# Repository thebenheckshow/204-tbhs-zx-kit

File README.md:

# 204-tbhs-zx-kit

Ben has modded many old computers into gaming portables and in this episode Ben returns to an old friend - the ZX Spectrum. He gets started by creating a schematic in eagle and designing a small PCB. Ben will conclude his journey in part 2.

Episode 204: Ben Heck's ZX Spectrum 2.0 Part 1 http://www.element14.com/community/docs/DOC-78511/l/episode-204-ben-hecks-zx-spectrum-20-part-1-episode

Episode 206: Ben Heck's ZX Spectrum 2.0 Part 2 http://www.element14.com/community/docs/DOC-78741/l/episode-206-ben-hecks-zx-spectrum-20-part-2-episode

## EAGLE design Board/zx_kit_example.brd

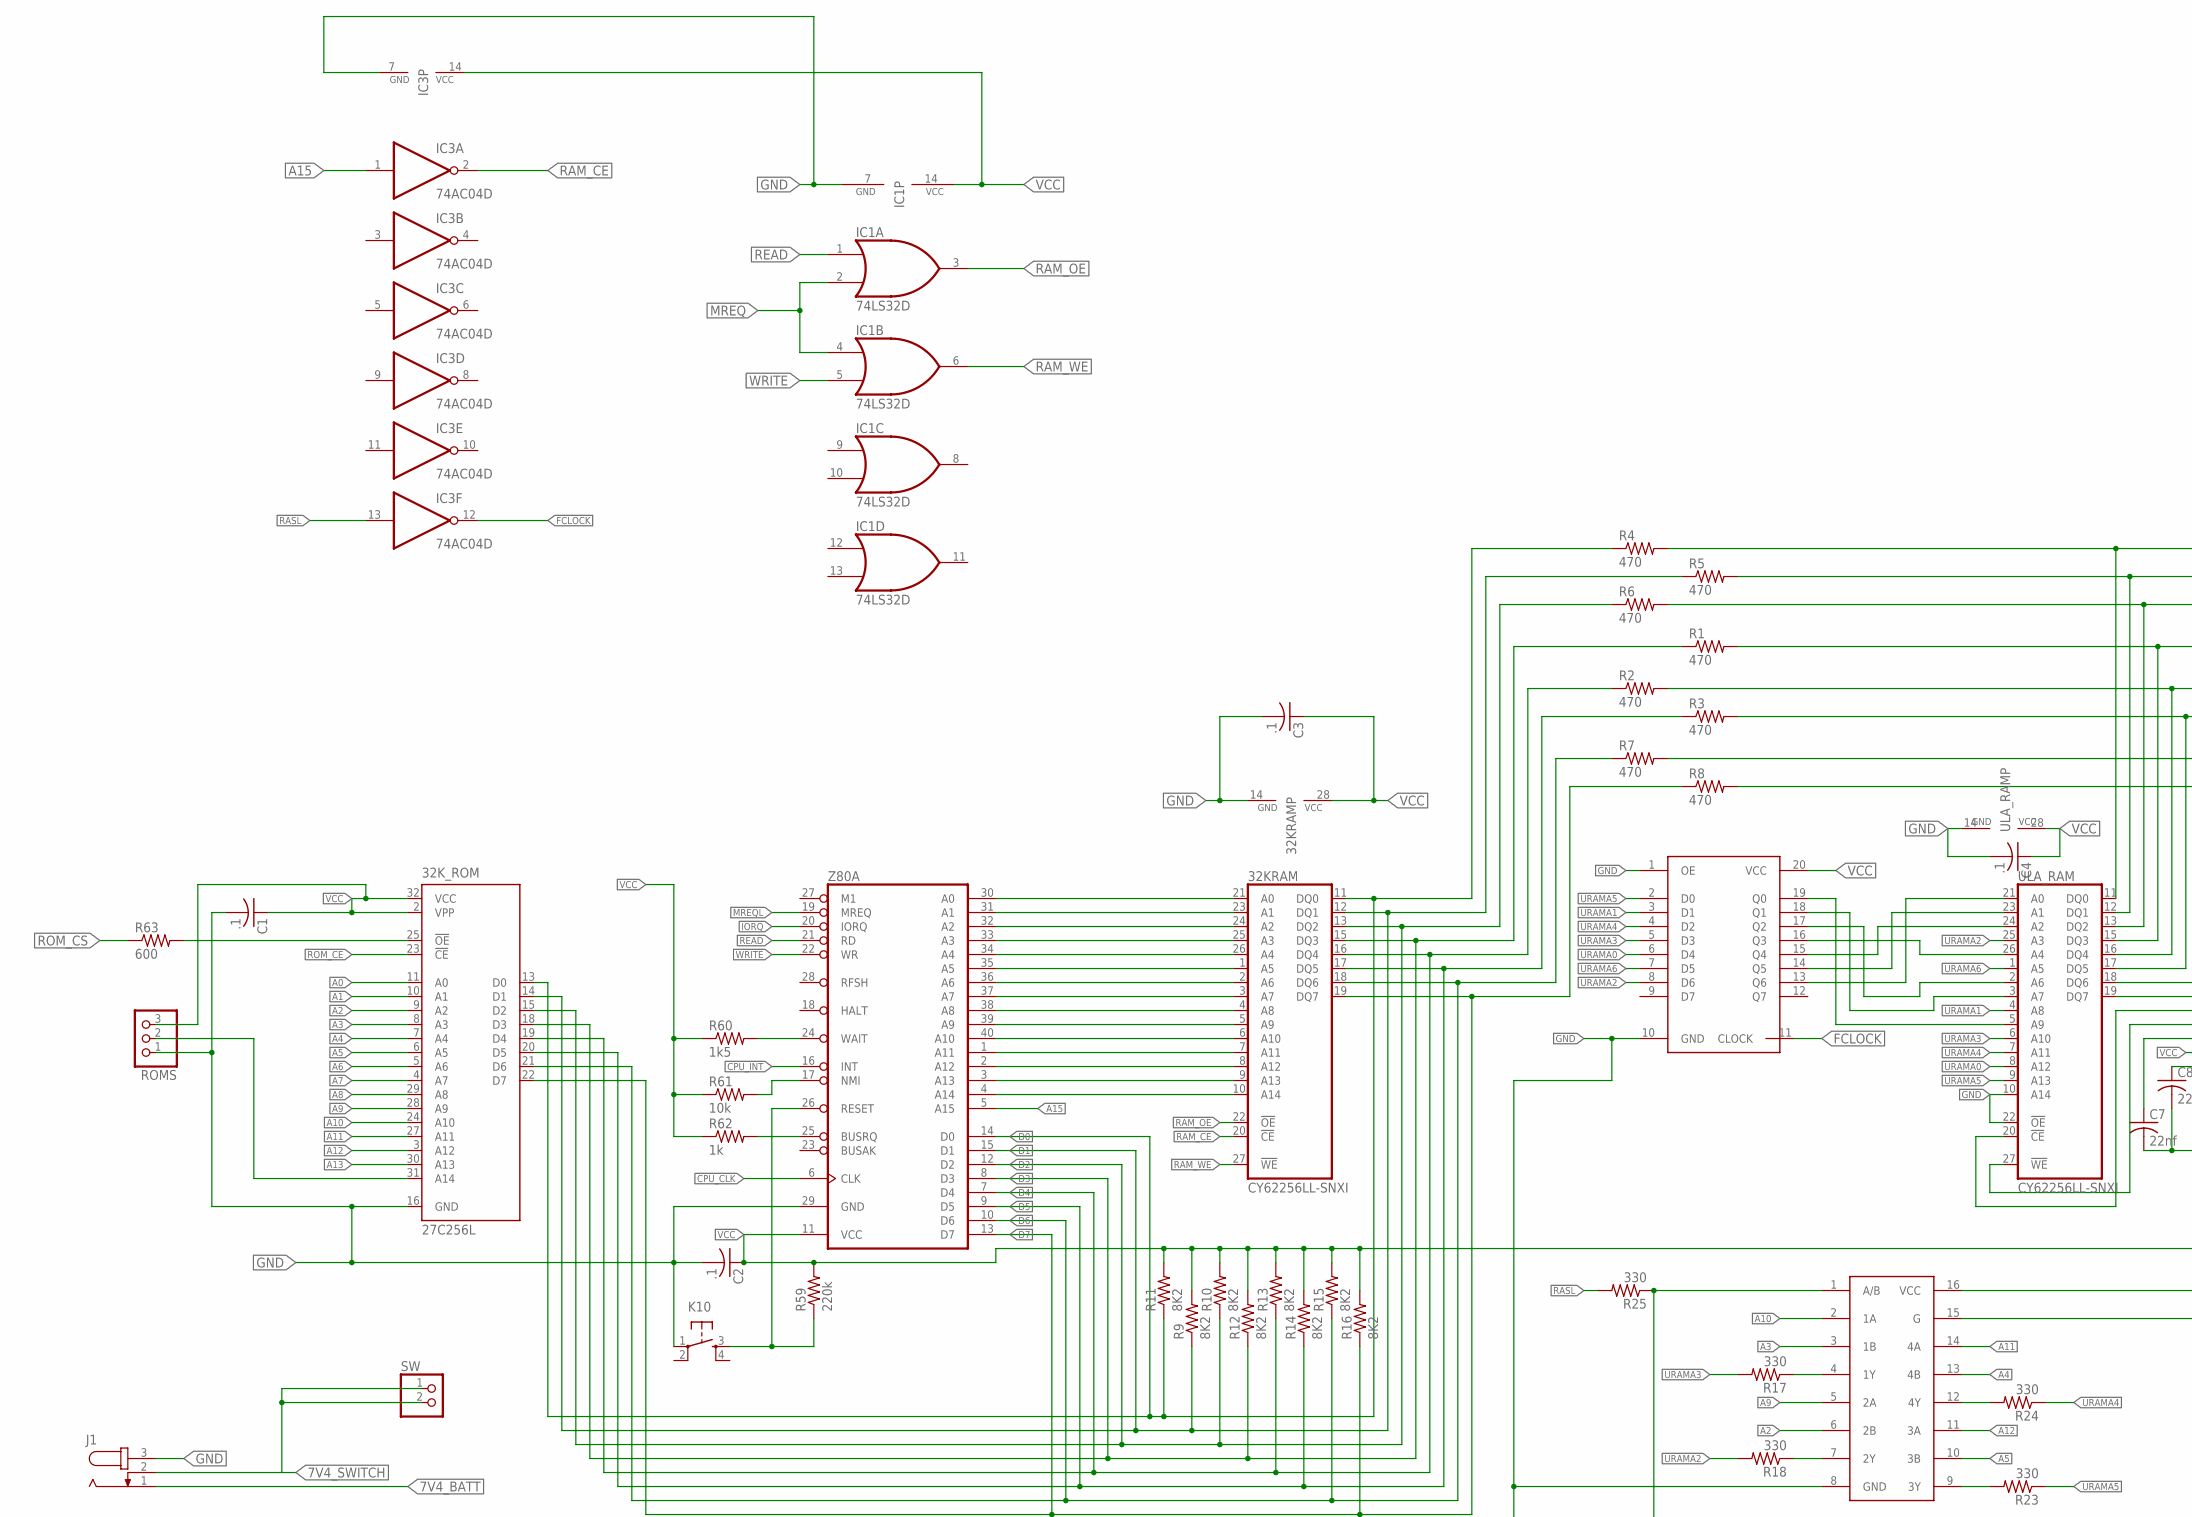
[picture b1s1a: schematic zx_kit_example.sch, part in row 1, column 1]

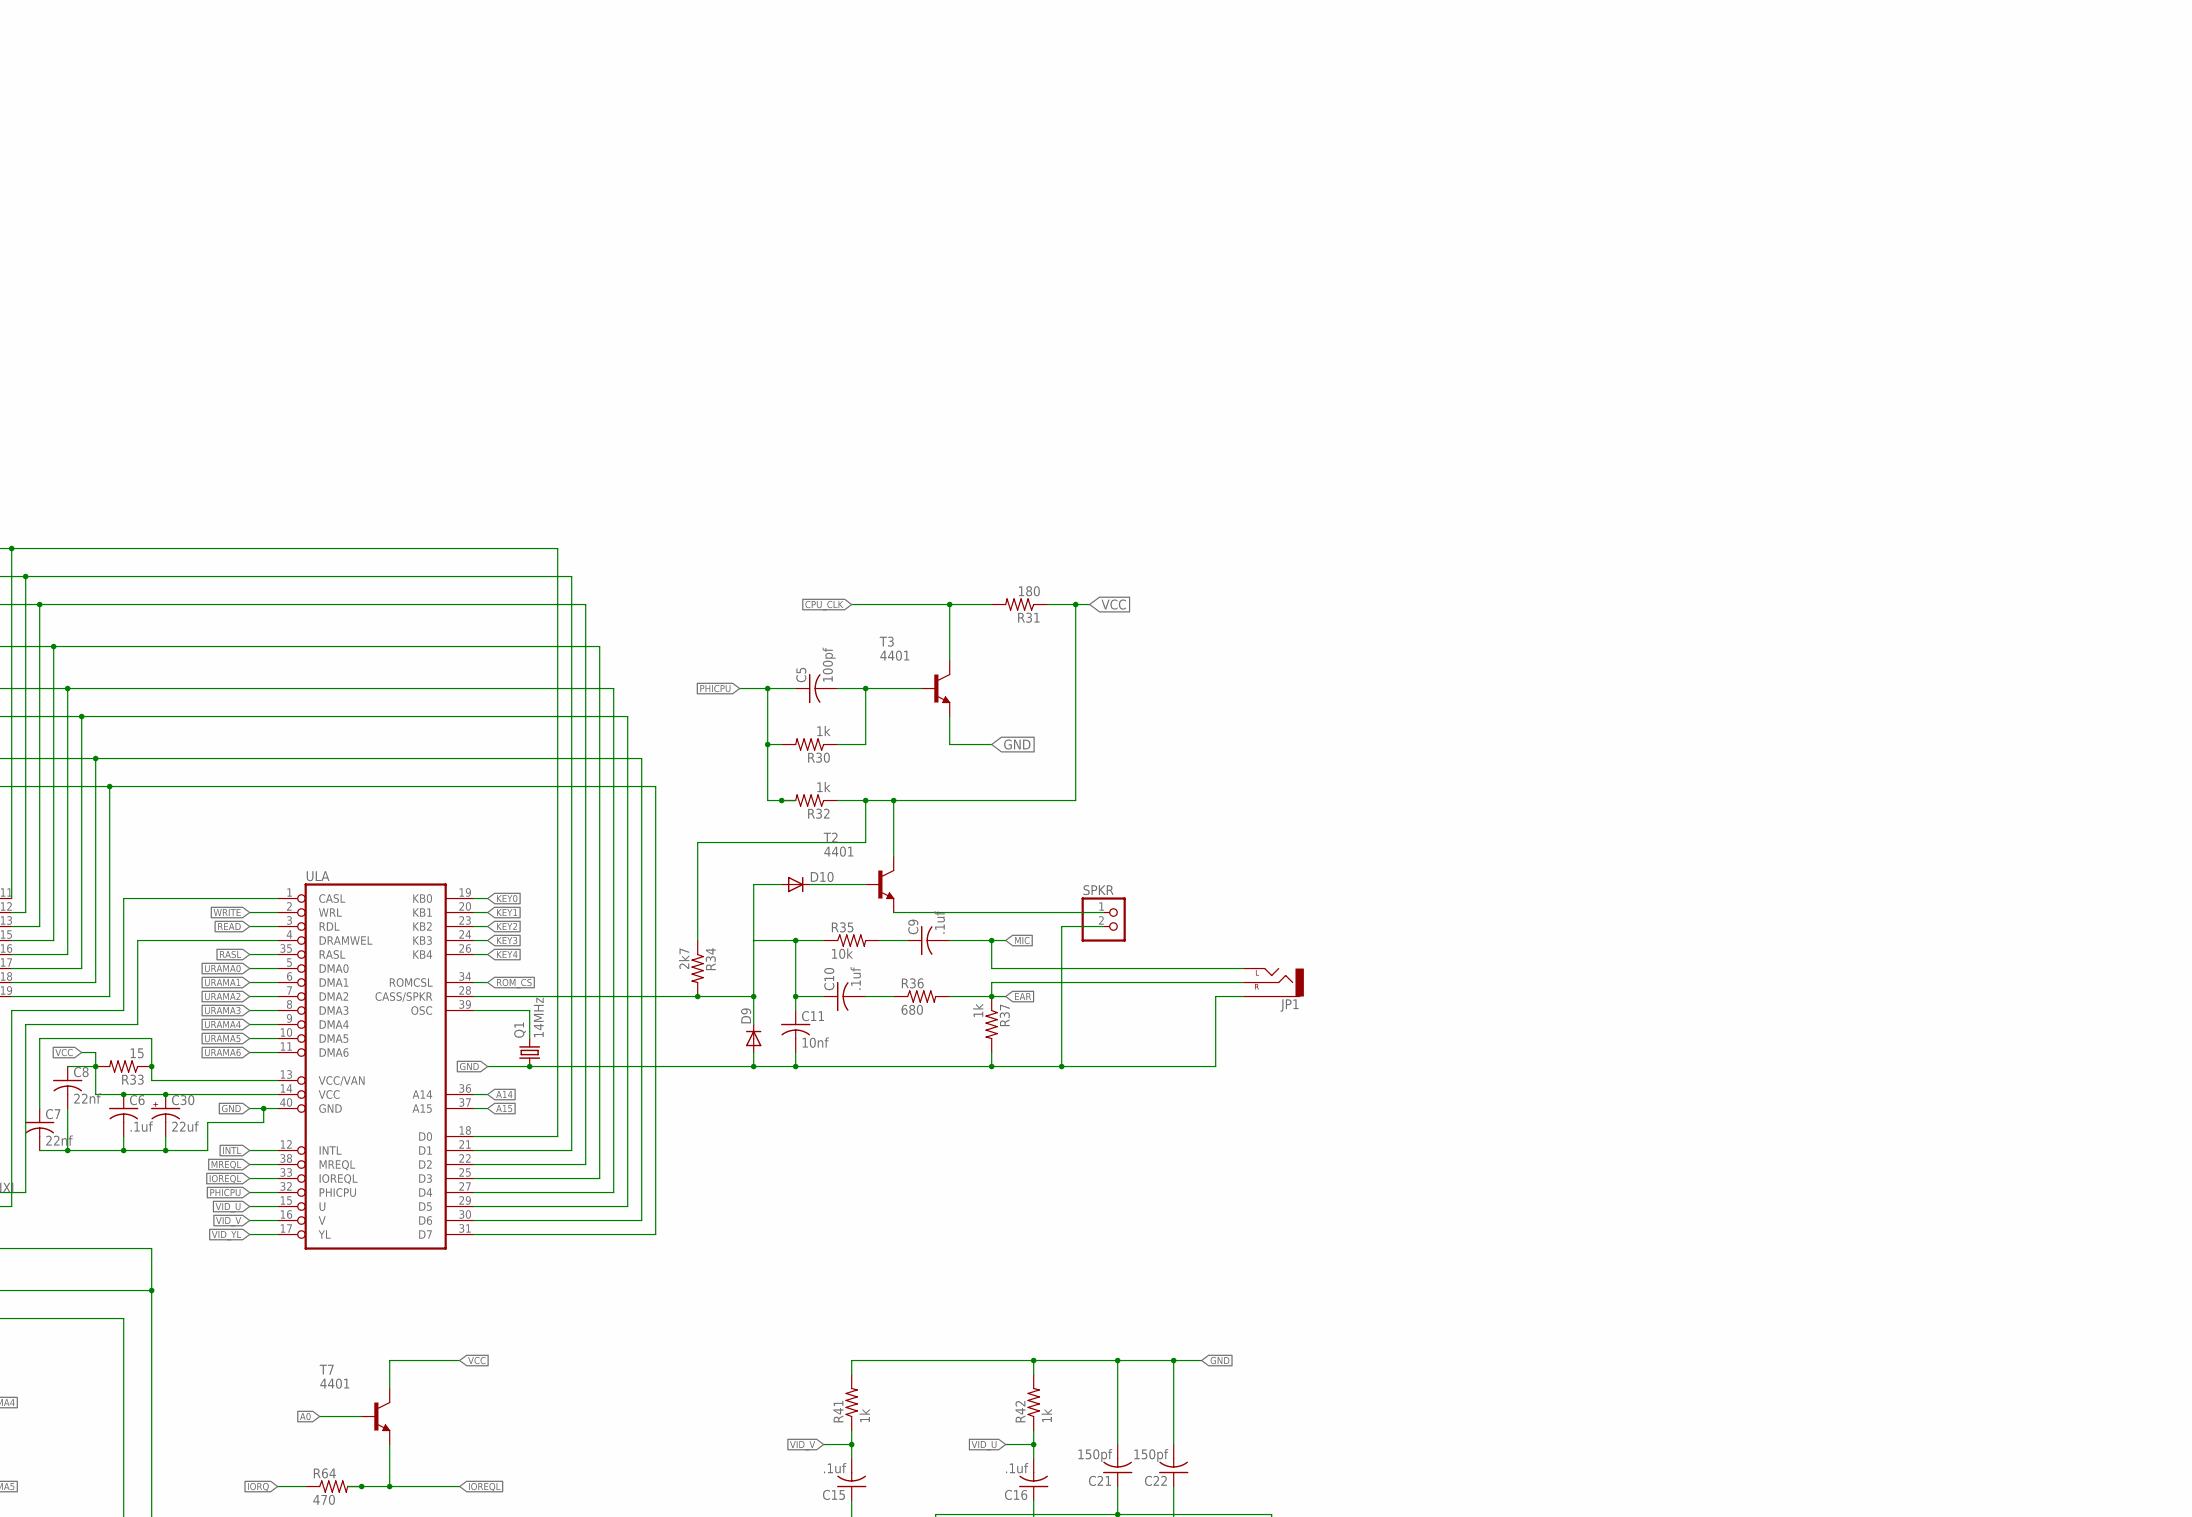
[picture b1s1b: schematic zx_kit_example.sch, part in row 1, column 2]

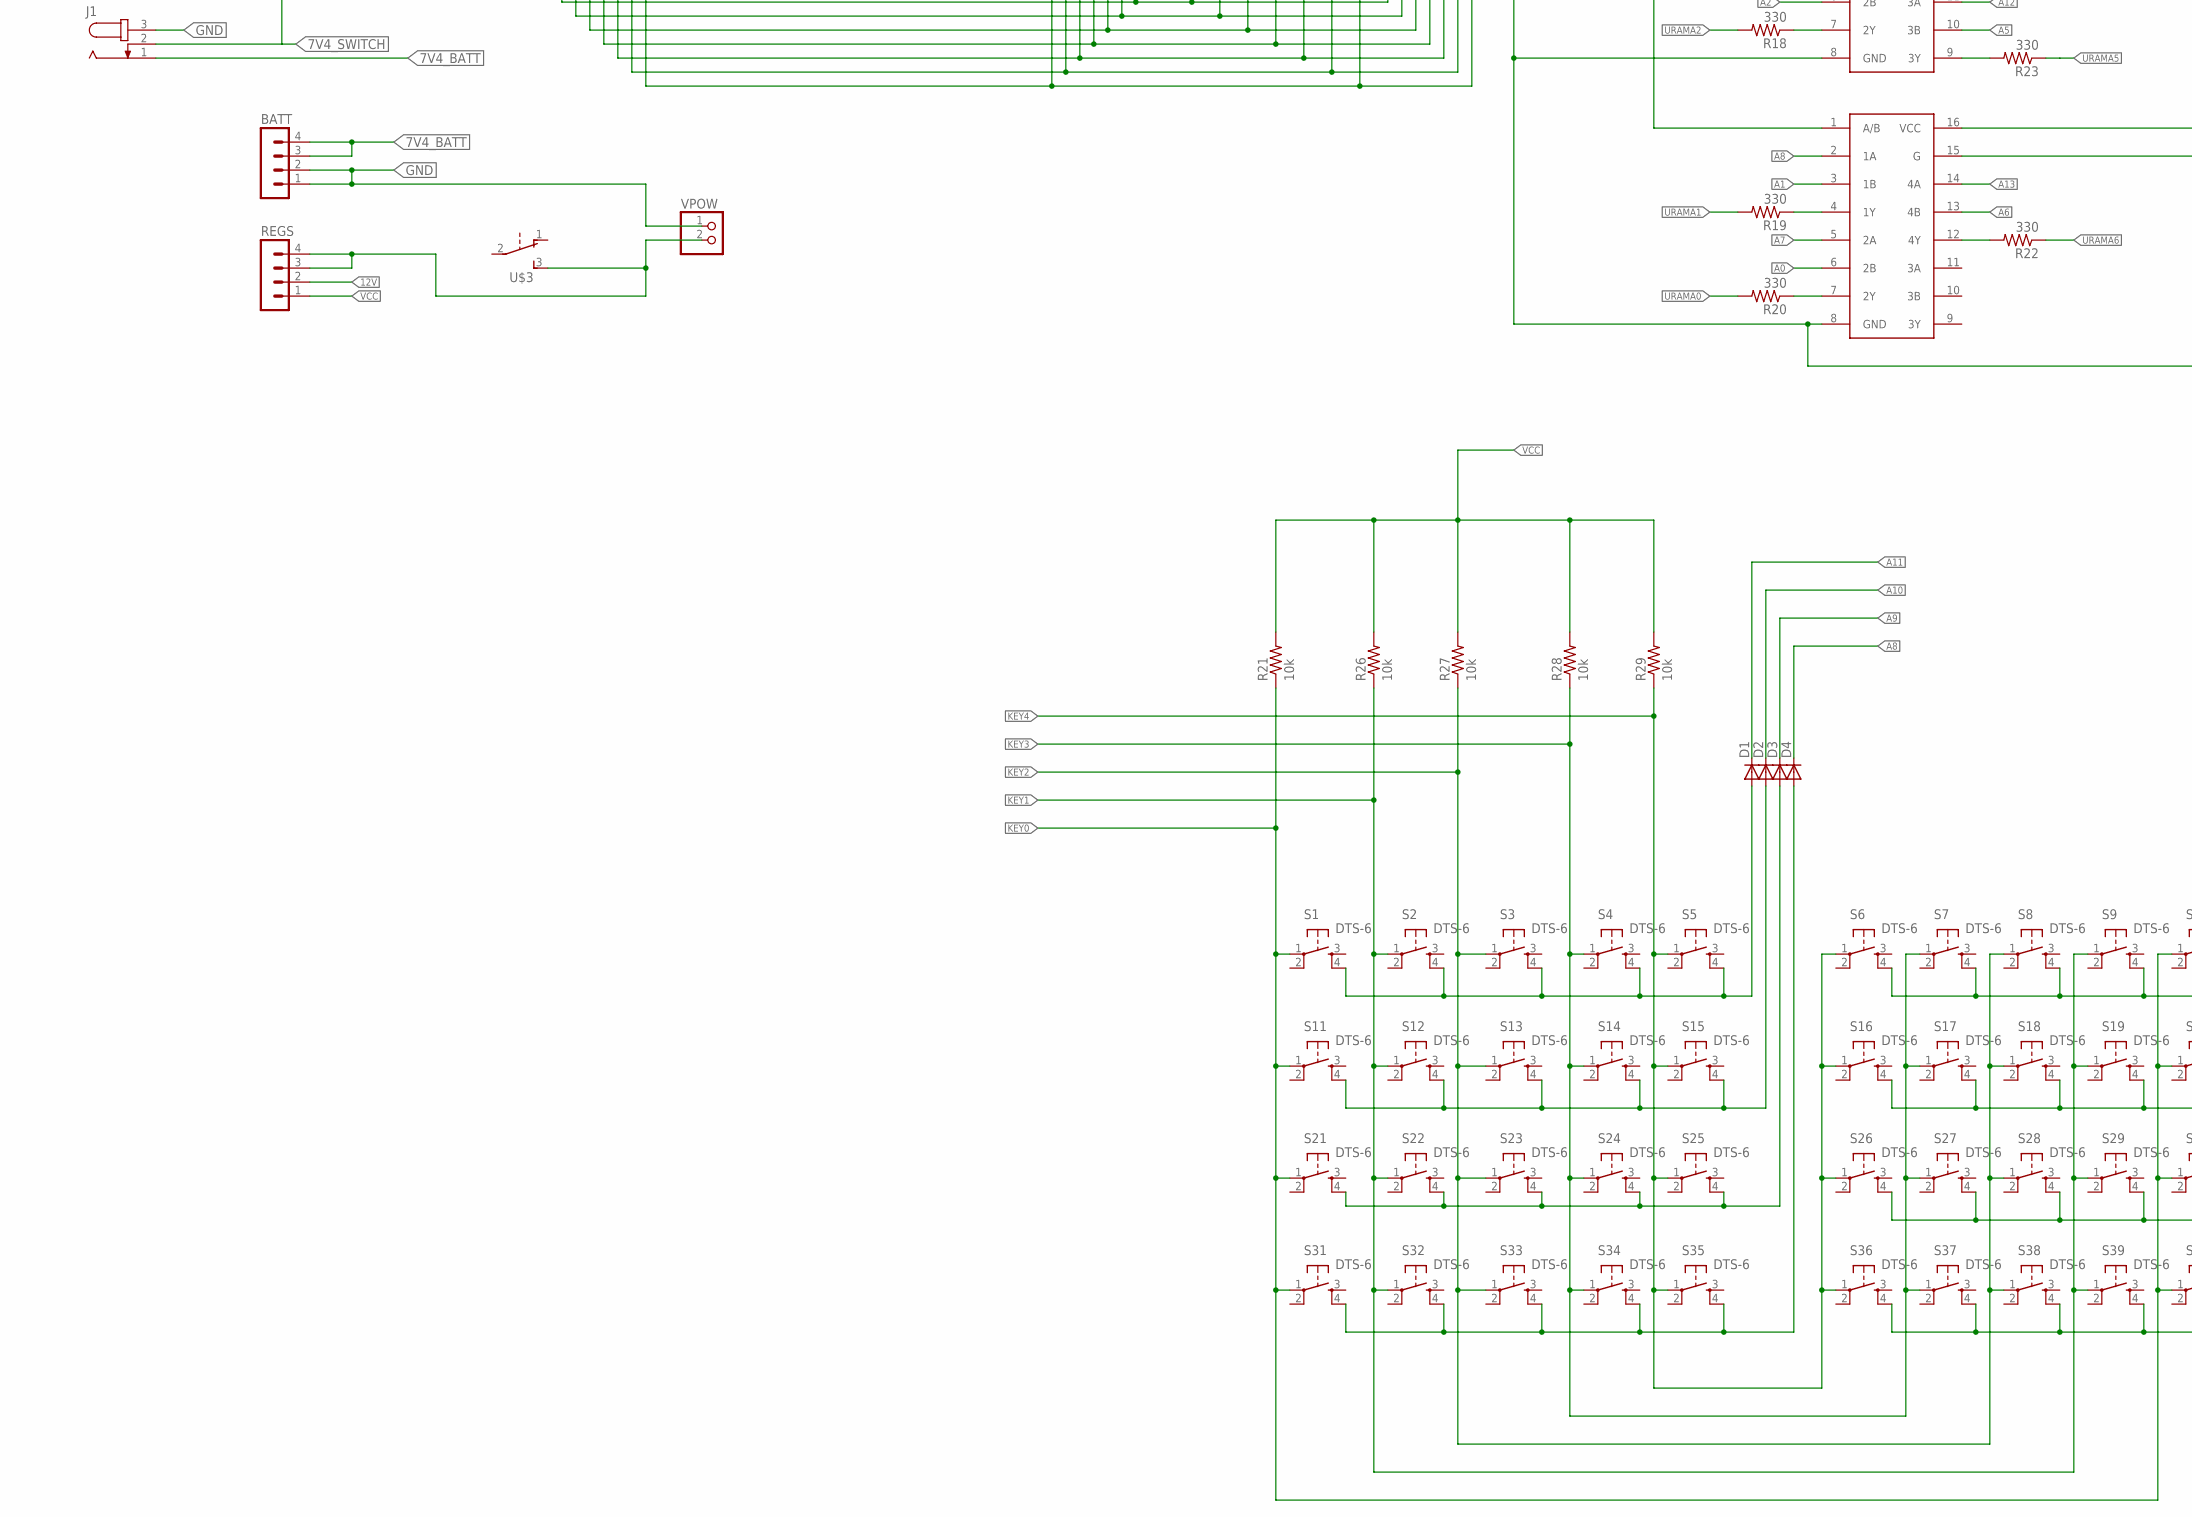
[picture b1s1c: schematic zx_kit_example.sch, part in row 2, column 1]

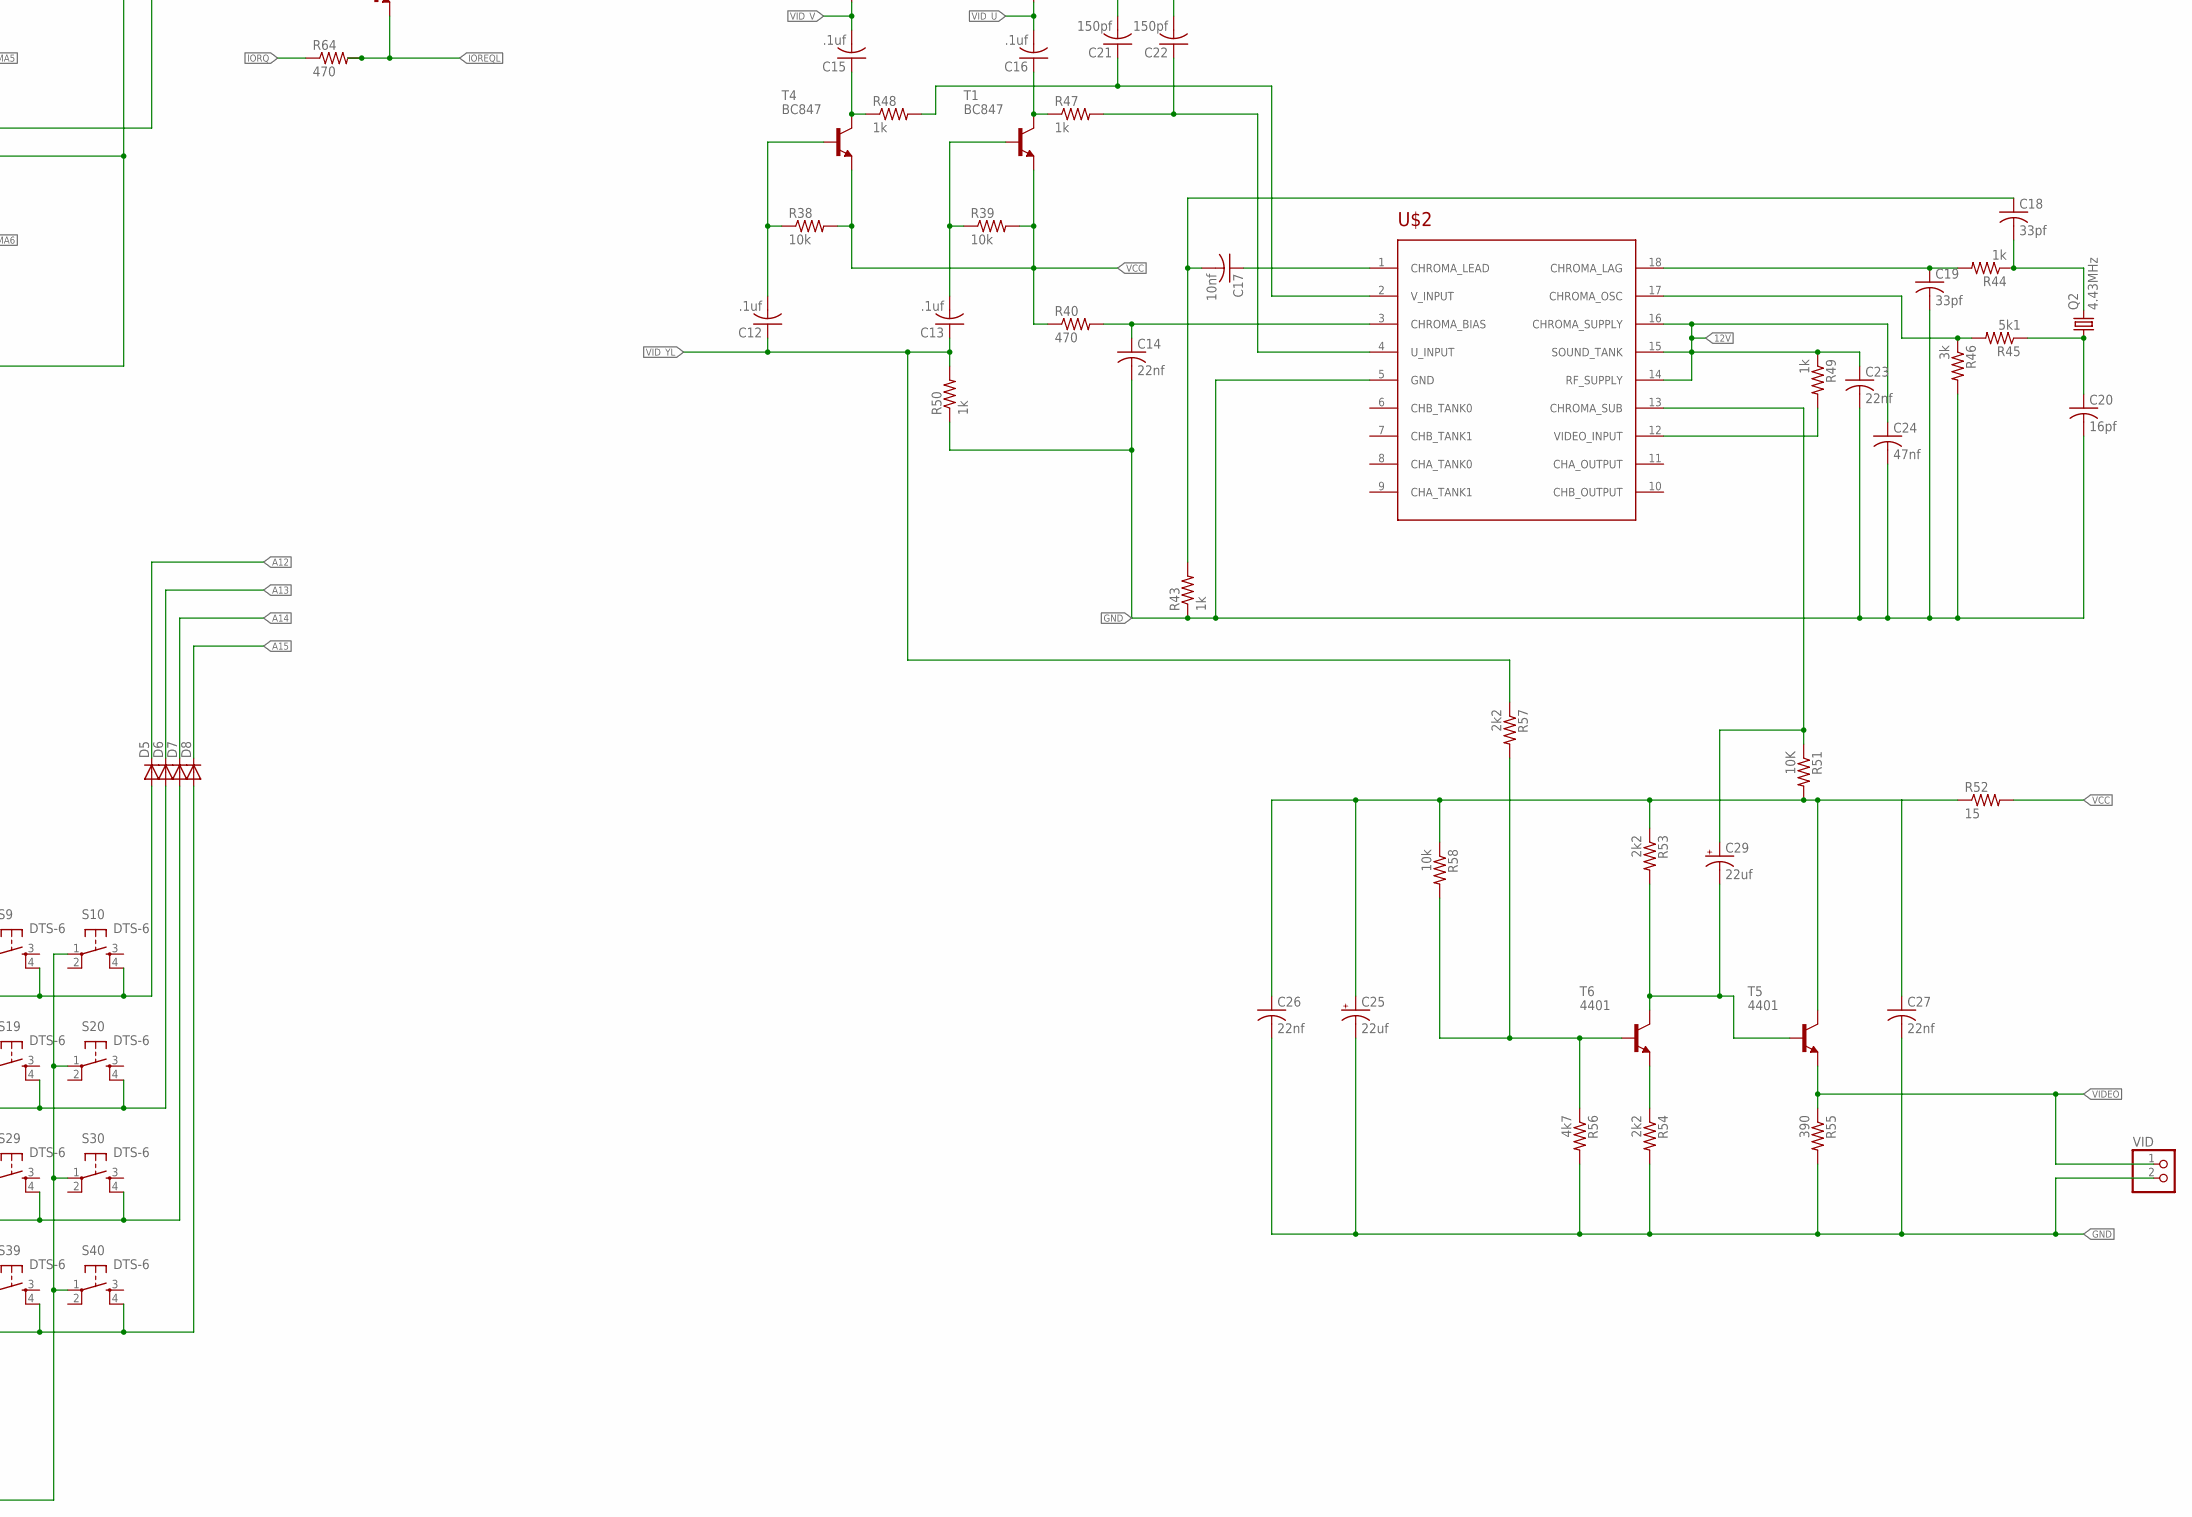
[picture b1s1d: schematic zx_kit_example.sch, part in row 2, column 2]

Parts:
32KRAM: CY62256LL-SNXI; SOJ28/3
32K_ROM: 27C256L; PLCC-32
157, 157-1: SN74HC157D; SO16
BATT: MA04-1
C1, C2, C3, C4: .1; C0805
C5: 100pf; C0805
C6, C9, C10, C12, C13, C15, C16: .1uf; C0805
C7, C8, C14, C23, C26, C27: 22nf; C0805
C11, C17: 10nf; C0805
C18, C19: 33pf; C0805
C20: 16pf; C0805
C21, C22: 150pf; C0805
C24: 47nf; C0805
C25, C29, C30: 22uf; PANASONIC_B
D1, D2, D3, D4, D5, D6, D7, D8, D9, D10: DIODE-SOD123; SOD123
IC1: 74LS32D; SO14
IC3: 74AC04D; SO14
J1: JACK-PLUG0; SPC4077
JP1: AUDIO-JACKPTH; AUDIO-JACK
K10: DTS-6
Q1: 14MHz; CTS406
Q2: 4.43MHz; HC49/S
R1, R2, R3, R4, R5, R6, R7, R8: 470; M0805
R9, R10, R11, R12, R13, R14, R15, R16: 8K2; M0805
R17, R18, R19, R20, R22, R23, R24, R25: 330; M0805
R21, R26, R27, R28, R29, R35, R38, R39, R58: 10k; R0805
R30, R32, R37, R41, R42, R43, R44, R47, R48, R49, R50: 1k; R0805
R31: 180; R0805
R33, R52: 15; R0805
R34: 2k7; R0805
R36: 680; R0805
R40, R64: 470; R0805
R45: 5k1; R0805
R46: 3k; R0805
R51: 10K; R0805
R53, R54, R57: 2k2; R0805
R55: 390; R0805
R56: 4k7; R0805
R59: 220k; M0805
R60: 1k5; M0805
R61: 10k; M0805
R62: 1k; M0805
R63: 600; M0805
REGS: MA04-1
ROMS: PINHD-1X3; 1X03
S1, S2, S3, S4, S5, S6, S7, S8, S9, S10, S11, S12, S13, S14, S15, S16, S17, S18, S19, S20, S21, S22, S23, S24, S25, S26, S27, S28, S29, S30, S31, S32, S33, S34, S35, S36, S37, S38, S39, S40: DTS-6
SPKR: PINHD-1X2; 1X02
SW: PINHD-1X2; 1X02
T1, T4: BC847; SOT23
T2, T3, T5, T6, T7: 4401; SOT23-BEC
U$1: MC74HC574A; SO20W
U$2: LM1889; SOCKET-18
U$3: MS12ASW30_01; MS12ASG30_01
ULA: ZXULA; DIL40
ULA_RAM: CY62256LL-SNXI; SOJ28/3
VID: PINHD-1X2; 1X02
VPOW: PINHD-1X2; 1X02
Z80A: Z80CPU; DIL40

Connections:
7V4_BATT: BATT.3, BATT.4, J1.1
7V4_SWITCH: J1.2, SW.1, SW.2
12V: C23.1, C24.1, R49.1, REGS.2, U$2.14 (RF_SUPPLY), U$2.15 (SOUND_TANK), U$2.16 (CHROMA_SUPPLY)
A0: 32KRAM.21 (A0), 32K_ROM.11 (A0), 157-1.6 (2B), T7.B, Z80A.30 (A0)
A1: 32KRAM.23 (A1), 32K_ROM.10 (A1), 157-1.3 (1B), Z80A.31 (A1)
A2: 32KRAM.24 (A2), 32K_ROM.9 (A2), 157.6 (2B), Z80A.32 (A2)
A3: 32KRAM.25 (A3), 32K_ROM.8 (A3), 157.3 (1B), Z80A.33 (A3)
A4: 32KRAM.26 (A4), 32K_ROM.7 (A4), 157.13 (4B), Z80A.34 (A4)
A5: 32KRAM.1 (A5), 32K_ROM.6 (A5), 157.10 (3B), Z80A.35 (A5)
A6: 32KRAM.2 (A6), 32K_ROM.5 (A6), 157-1.13 (4B), Z80A.36 (A6)
A7: 32KRAM.3 (A7), 32K_ROM.4 (A7), 157-1.5 (2A), Z80A.37 (A7)
A8: 32KRAM.4 (A8), 32K_ROM.29 (A8), 157-1.2 (1A), D4.C, Z80A.38 (A8)
A9: 32KRAM.5 (A9), 32K_ROM.28 (A9), 157.5 (2A), D3.C, Z80A.39 (A9)
A10: 32KRAM.6 (A10), 32K_ROM.24 (A10), 157.2 (1A), D2.C, Z80A.40 (A10)
A11: 32KRAM.7 (A11), 32K_ROM.27 (A11), 157.14 (4A), D1.C, Z80A.1 (A11)
A12: 32KRAM.8 (A12), 32K_ROM.3 (A12), 157.11 (3A), D5.C, Z80A.2 (A12)
A13: 32KRAM.9 (A13), 32K_ROM.30 (A13), 157-1.14 (4A), D6.C, Z80A.3 (A13)
A14: 32KRAM.10 (A14), D7.C, ULA.36 (A14), Z80A.4 (A14)
A15: D8.C, IC3.1 (I), ULA.37 (A15), Z80A.5 (A15)
CASL: ULA.1 (CASL), ULA_RAM.20 (!CE)
CASS: C10.1, C11.1, D9.C, D10.A, R34.2, R35.1, ULA.28 (CASS/SPKR)
CPU_CLK: R31.2, T3.C, Z80A.6 (CLK)
CPU_INT: Z80A.16 (INT)
CPU_RESET: K10.3, R59.1, Z80A.26 (RESET)
D0: 32KRAM.11 (DQ0), 32K_ROM.13 (D0), R4.1, R11.1, Z80A.14 (D0)
D1: 32KRAM.12 (DQ1), 32K_ROM.14 (D1), R5.1, R9.1, Z80A.15 (D1)
D2: 32KRAM.13 (DQ2), 32K_ROM.15 (D2), R6.1, R10.1, Z80A.12 (D2)
D3: 32KRAM.15 (DQ3), 32K_ROM.18 (D3), R1.1, R12.1, Z80A.8 (D3)
D4: 32KRAM.16 (DQ4), 32K_ROM.19 (D4), R2.1, R13.1, Z80A.7 (D4)
D5: 32KRAM.17 (DQ5), 32K_ROM.20 (D5), R3.1, R14.1, Z80A.9 (D5)
D6: 32KRAM.18 (DQ6), 32K_ROM.21 (D6), R7.1, R15.1, Z80A.10 (D6)
D7: 32KRAM.19 (DQ7), 32K_ROM.22 (D7), R8.1, R16.1, Z80A.13 (D7)
DRAWMWEL: ULA.4 (DRAMWEL), ULA_RAM.27 (!WE)
EAR: JP1.RING (RIGHT), R36.2, R37.1
FCLOCK: IC3.12 (O), U$1.11 (CLOCK)
FLIPCLOCK: U$1.19 (Q0), ULA_RAM.5 (A9)
GND: 32KRAM.14 (GND), 32K_ROM.16 (GND), 157.8 (GND), 157.15 (G), 157-1.8 (GND), 157-1.15 (G), BATT.1, BATT.2, C1.2, C2.2, C3.2, C4.2, C6.2, C7.2, C8.2, C11.2, C14.2, C19.2, C20.2, C21.2, C22.2, C23.2, C24.2, C25.-, C26.2, C27.2, C30.-, D9.A, IC1.7 (GND), IC3.7 (GND), J1.3, JP1.SLEEVE, K10.1, Q1.1, R37.2, R41.2, R42.2, R43.1, R46.2, R50.1, R54.2, R55.2, R56.2, ROMS.1, SPKR.2, T3.E, U$1.1 (OE), U$1.10 (GND), U$2.5 (GND), ULA.40 (GND), ULA_RAM.10 (A14), ULA_RAM.14 (GND), ULA_RAM.22 (!OE), VID.2, VPOW.1, Z80A.29 (GND)
INTL: ULA.12 (INTL)
IOREQL: R64.2, T7.E, ULA.33 (IOREQL)
IORQ: R64.1, Z80A.20 (IORQ)
KEY0: R21.1, S1.1, S10.1, S11.1, S20.1, S21.1, S30.1, S31.1, S40.1, ULA.19 (KB0)
KEY1: R26.1, S2.1, S9.1, S12.1, S19.1, S22.1, S29.1, S32.1, S39.1, ULA.20 (KB1)
KEY2: R27.1, S3.1, S8.1, S13.1, S18.1, S23.1, S28.1, S33.1, S38.1, ULA.23 (KB2)
KEY3: R28.1, S4.1, S7.1, S14.1, S17.1, S24.1, S27.1, S34.1, S37.1, ULA.24 (KB3)
KEY4: R29.1, S5.1, S6.1, S15.1, S16.1, S25.1, S26.1, S35.1, S36.1, ULA.26 (KB4)
MIC: C9.2, JP1.TIP (LEFT)
MREQ: IC1.2 (I1), IC1.4 (I0)
MREQL: ULA.38 (MREQL), Z80A.19 (MREQ)
unnamed: 32K_ROM.25 (!OE), R63.2
unnamed: R4.2, ULA.18 (D0), ULA_RAM.11 (DQ0)
unnamed: R5.2, ULA.21 (D1), ULA_RAM.12 (DQ1)
unnamed: R6.2, ULA.22 (D2), ULA_RAM.13 (DQ2)
unnamed: R1.2, ULA.25 (D3), ULA_RAM.15 (DQ3)
unnamed: R2.2, ULA.27 (D4), ULA_RAM.16 (DQ4)
unnamed: R3.2, ULA.29 (D5), ULA_RAM.17 (DQ5)
unnamed: R7.2, ULA.30 (D6), ULA_RAM.18 (DQ6)
unnamed: R8.2, ULA.31 (D7), ULA_RAM.19 (DQ7)
unnamed: U$1.13 (Q6), ULA_RAM.21 (A0)
unnamed: U$1.14 (Q5), ULA_RAM.23 (A1)
unnamed: U$1.15 (Q4), ULA_RAM.24 (A2)
unnamed: U$1.16 (Q3), ULA_RAM.26 (A4)
unnamed: U$1.17 (Q2), ULA_RAM.2 (A6)
unnamed: 157.4 (1Y), R17.1
unnamed: Q1.3 (2), ULA.39 (OSC)
unnamed: 157.7 (2Y), R18.1
unnamed: U$1.18 (Q1), ULA_RAM.3 (A7)
unnamed: 157-1.4 (1Y), R19.1
unnamed: 157-1.7 (2Y), R20.1
unnamed: C5.2, R30.1, T3.B
unnamed: C12.2, R38.1, T4.1 (B)
unnamed: D10.C, T2.B
unnamed: C9.1, R35.2
unnamed: 157-1.12 (4Y), R22.2
unnamed: D1.A, S1.4, S2.4, S3.4, S4.4, S5.4
unnamed: D2.A, S11.4, S12.4, S13.4, S14.4, S15.4
unnamed: R60.2, Z80A.24 (WAIT)
unnamed: D3.A, S21.4, S22.4, S23.4, S24.4, S25.4
unnamed: D4.A, S31.4, S32.4, S33.4, S34.4, S35.4
unnamed: 157.1 (A/B), 157-1.1 (A/B), R25.1
unnamed: D5.A, S6.4, S7.4, S8.4, S9.4, S10.4
unnamed: D6.A, S16.4, S17.4, S18.4, S19.4, S20.4
unnamed: 157.9 (3Y), R23.2
unnamed: D7.A, S26.4, S27.4, S28.4, S29.4, S30.4
unnamed: D8.A, S36.4, S37.4, S38.4, S39.4, S40.4
unnamed: 157.12 (4Y), R24.2
unnamed: C13.2, R39.1, T1.1 (B)
unnamed: C10.2, R36.1
unnamed: C14.1, R40.2, U$2.3 (CHROMA_BIAS)
unnamed: C15.1, R48.1, T4.3 (C)
unnamed: 32K_ROM.31 (A14), ROMS.2
unnamed: C16.1, R47.1, T1.3 (C)
unnamed: R49.2, U$2.12 (VIDEO_INPUT)
unnamed: C17.1, U$2.1 (CHROMA_LEAD)
unnamed: C17.2, C18.1, R43.2
unnamed: C19.1, R44.2, U$2.18 (CHROMA_LAG)
unnamed: C18.2, Q2.2, R44.1
unnamed: R45.2, R46.1, U$2.17 (CHROMA_OSC)
unnamed: C22.1, R47.2, U$2.4 (U_INPUT)
unnamed: C20.1, Q2.1, R45.1
unnamed: C21.1, R48.2, U$2.2 (V_INPUT)
unnamed: C29.+, R51.1, U$2.13 (CHROMA_SUB)
unnamed: R61.2, Z80A.17 (NMI)
unnamed: C25.+, C26.1, C27.1, R51.2, R52.1, R53.1, R58.1, T5.C
unnamed: C29.-, R53.2, T5.B, T6.C
unnamed: R54.1, T6.E
unnamed: R62.2, Z80A.25 (BUSRQ)
unnamed: R56.1, R57.2, R58.2, T6.B
unnamed: REGS.3, REGS.4, U$3.3 (S), VPOW.2
PHICPU: C5.1, R30.2, R32.2, ULA.32 (PHICPU)
RAM_CE: 32KRAM.20 (!CE), IC3.2 (O)
RAM_OE: 32KRAM.22 (!OE), IC1.3 (O)
RAM_WE: 32KRAM.27 (!WE), IC1.6 (O)
RASL: IC3.13 (I), R25.2, ULA.35 (RASL)
READ: IC1.1 (I0), ULA.3 (RDL), Z80A.21 (RD)
ROM_CE: 32K_ROM.23 (!CE)
ROM_CS: R63.1, ULA.34 (ROMCSL)
SPEAKER: SPKR.1, T2.E
URAMA0: R20.2, U$1.6 (D4), ULA.5 (DMA0), ULA_RAM.8 (A12)
URAMA1: R19.2, U$1.3 (D1), ULA.6 (DMA1), ULA_RAM.4 (A8)
URAMA2: R18.2, U$1.8 (D6), ULA.7 (DMA2), ULA_RAM.25 (A3)
URAMA3: R17.2, U$1.5 (D3), ULA.8 (DMA3), ULA_RAM.6 (A10)
URAMA4: R24.1, U$1.4 (D2), ULA.9 (DMA4), ULA_RAM.7 (A11)
URAMA5: R23.1, U$1.2 (D0), ULA.10 (DMA5), ULA_RAM.9 (A13)
URAMA6: R22.1, U$1.7 (D5), ULA.11 (DMA6), ULA_RAM.1 (A5)
VCC: 32KRAM.28 (VCC), 32K_ROM.2 (VPP), 32K_ROM.32 (VCC), 157.16 (VCC), 157-1.16 (VCC), C1.1, C2.1, C3.1, C4.1, C6.1, C8.1, C30.+, IC1.14 (VCC), IC3.14 (VCC), R9.2, R10.2, R11.2, R12.2, R13.2, R14.2, R15.2, R16.2, R21.2, R26.2, R27.2, R28.2, R29.2, R31.1, R32.1, R33.2, R34.1, R38.2, R39.2, R40.1, R52.2, R59.2, R60.1, R61.1, R62.1, REGS.1, ROMS.3, T1.2 (E), T2.C, T4.2 (E), T7.C, U$1.20 (VCC), ULA.14 (VCC), ULA_RAM.28 (VCC), Z80A.11 (VCC)
VCC/VAN: C7.1, R33.1, ULA.13 (VCC/VAN)
VIDEO: R55.1, T5.E, VID.1
VID_U: C16.2, R42.1, ULA.15 (U)
VID_V: C15.2, R41.1, ULA.16 (V)
VID_YL: C12.1, C13.1, R50.2, R57.1, ULA.17 (YL)
WRITE: IC1.5 (I1), ULA.2 (WRL), Z80A.22 (WR)

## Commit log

2015-11-03 initial comit
2015-11-03 BOM added
2015-11-05 Update README.md
    Removed incorrect tracking codes on links

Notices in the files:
parts and their libraries:
SparkFun-Connectors: Licensing: Creative Commons ShareAlike 4.0 International - https://creativecommons.org/licenses/by-sa/4.0
